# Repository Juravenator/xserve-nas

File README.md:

# xServe infra deployer

This repo is used to manage the NixOS server.

## Quick start

- Check up on CI/CD sync jobs status:
  See the [CICD docs](./docs/cicd.md).
- Sync a specific server on the local machine:
  See the [manually syncing](./docs/manual-sync.md) docs.
- Add a new server, or recommission an existing one:  
  See the docs in [the init folder](./init).

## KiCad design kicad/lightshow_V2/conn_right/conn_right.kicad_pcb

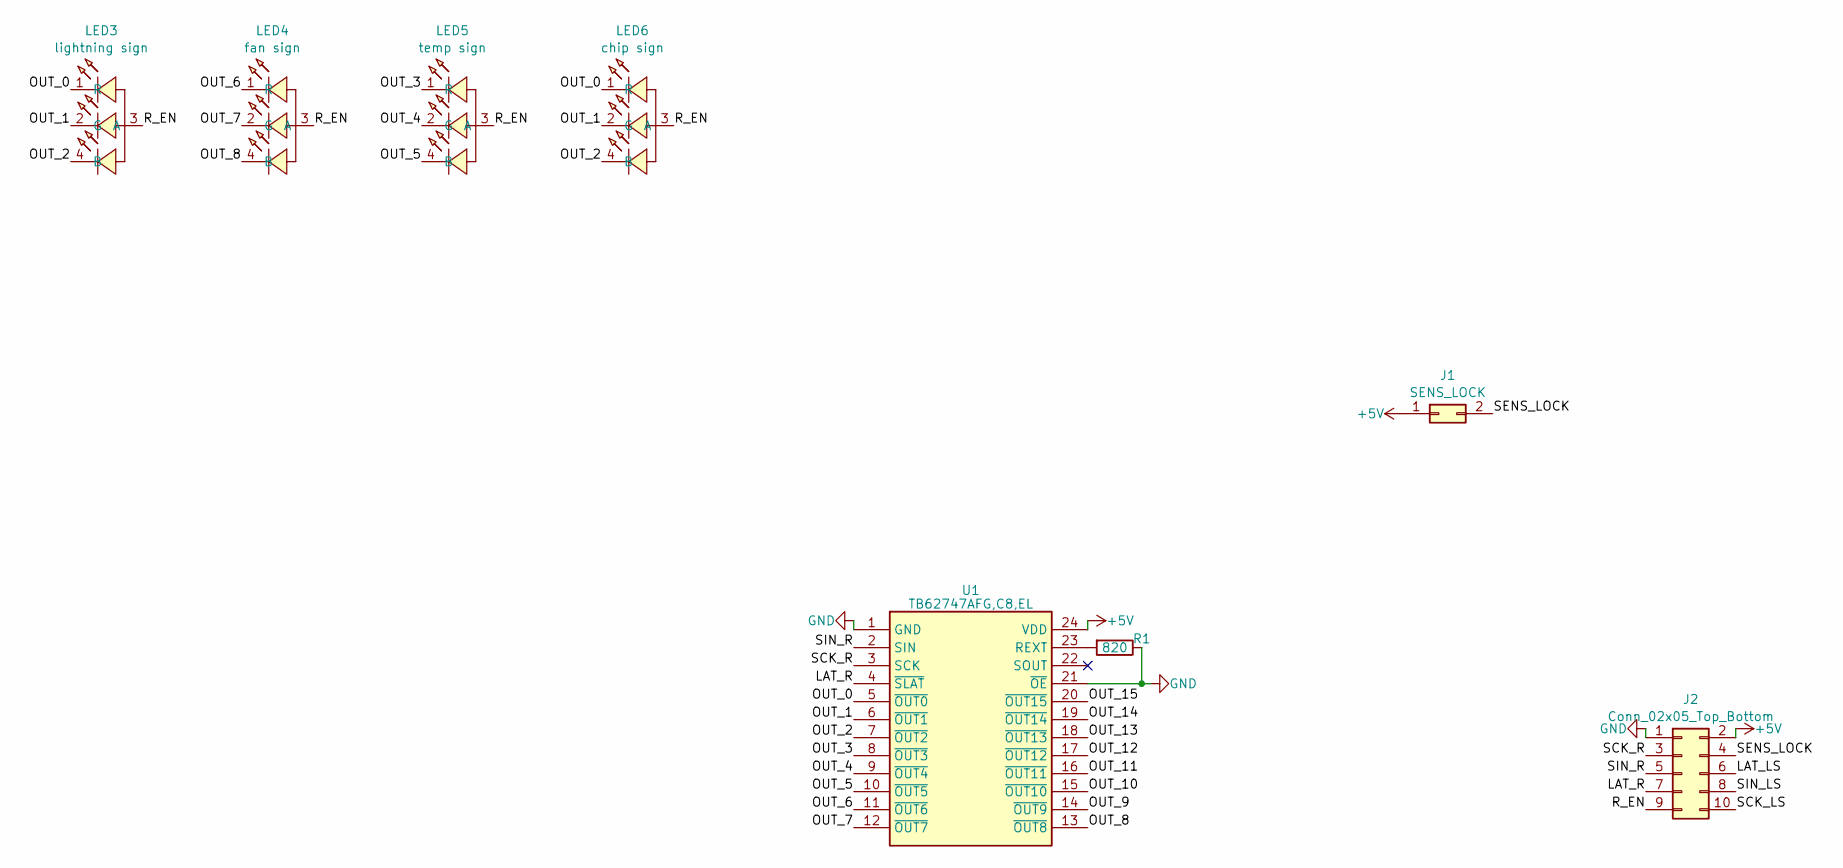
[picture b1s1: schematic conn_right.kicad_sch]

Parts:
J1: SENS_LOCK; PinHeader_1x02_P1.50mm_Vertical
J2: Conn_02x05_Top_Bottom; PinHeader_2x05_P2.00mm_Vertical_SMD
LED3: lightning sign; LED RGB XINGLIGHT XL-2012RGBC 0805; LCSC Part C965848
LED4: fan sign; LED RGB XINGLIGHT XL-2012RGBC 0805; LCSC Part C965848
LED5: temp sign; LED RGB XINGLIGHT XL-2012RGBC 0805; LCSC Part C965848
LED6: chip sign; LED RGB XINGLIGHT XL-2012RGBC 0805; LCSC Part C965848
R1: 820; R_0603_1608Metric
U1: TB62747AFG,C8,EL; SOP100P800X190-24N; Mouser Part Number 757-TB62747AFG,C8,EL

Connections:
+5V: J1.1, J2.2, U1.24 (VDD)
/LAT_LS: J2.6
/LAT_R: J2.7, U1.4 (~SLAT)
/OUT_0: LED3.1 (R), LED6.1 (R), U1.5 (~OUT0)
/OUT_1: LED3.2 (G), LED6.2 (G), U1.6 (~OUT1)
/OUT_2: LED3.4 (B), LED6.4 (B), U1.7 (~OUT2)
/OUT_3: LED5.1 (R), U1.8 (~OUT3)
/OUT_4: LED5.2 (G), U1.9 (~OUT4)
/OUT_5: LED5.4 (B), U1.10 (~OUT5)
/OUT_6: LED4.1 (R), U1.11 (~OUT6)
/OUT_7: LED4.2 (G), U1.12 (~OUT7)
/OUT_8: LED4.4 (B), U1.13 (~OUT8)
/OUT_9: U1.14 (~OUT9)
/OUT_10: U1.15 (~OUT10)
/OUT_11: U1.16 (~OUT11)
/OUT_12: U1.17 (~OUT12)
/OUT_13: U1.18 (~OUT13)
/OUT_14: U1.19 (~OUT14)
/OUT_15: U1.20 (~OUT15)
/R_EN: J2.9, LED3.3 (A), LED4.3 (A), LED5.3 (A), LED6.3 (A)
/SCK_LS: J2.10
/SCK_R: J2.3, U1.3 (SCK)
/SENS_LOCK: J1.2, J2.4
/SIN_LS: J2.8
/SIN_R: J2.5, U1.2 (SIN)
GND: J2.1, R1.1, U1.1 (GND), U1.21 (~OE)
unnamed: R1.2, U1.23 (REXT)

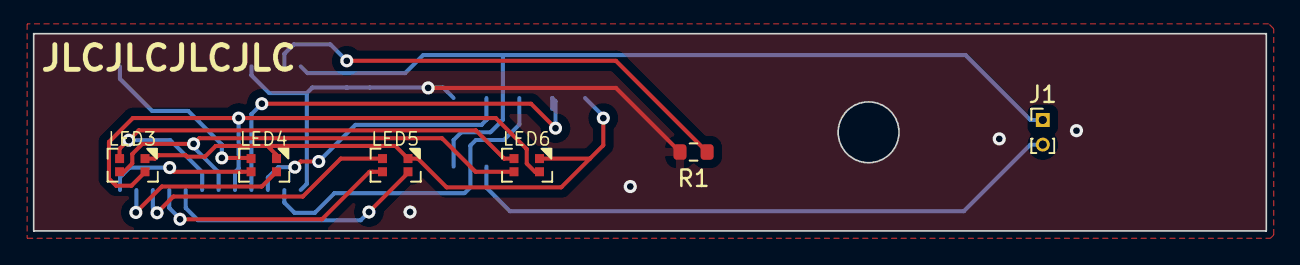
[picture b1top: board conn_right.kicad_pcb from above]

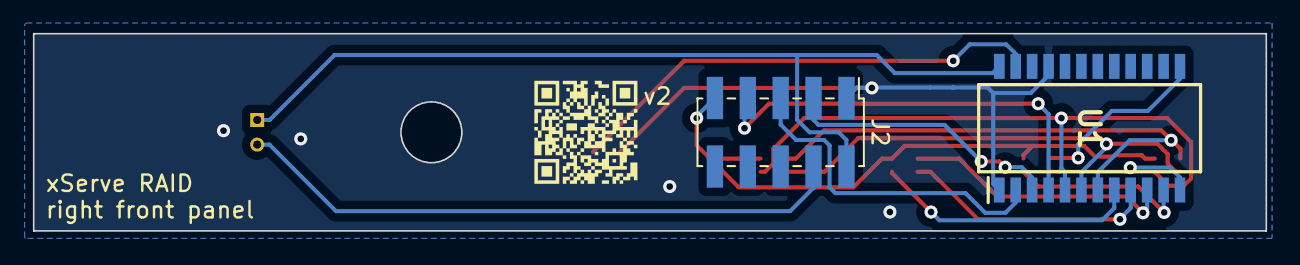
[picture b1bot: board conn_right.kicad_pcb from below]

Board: 2 copper layers, 75.0 x 12.0 mm, 9 parts (3 on the bottom side), 17 nets.

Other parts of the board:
v2: LOGO; qr

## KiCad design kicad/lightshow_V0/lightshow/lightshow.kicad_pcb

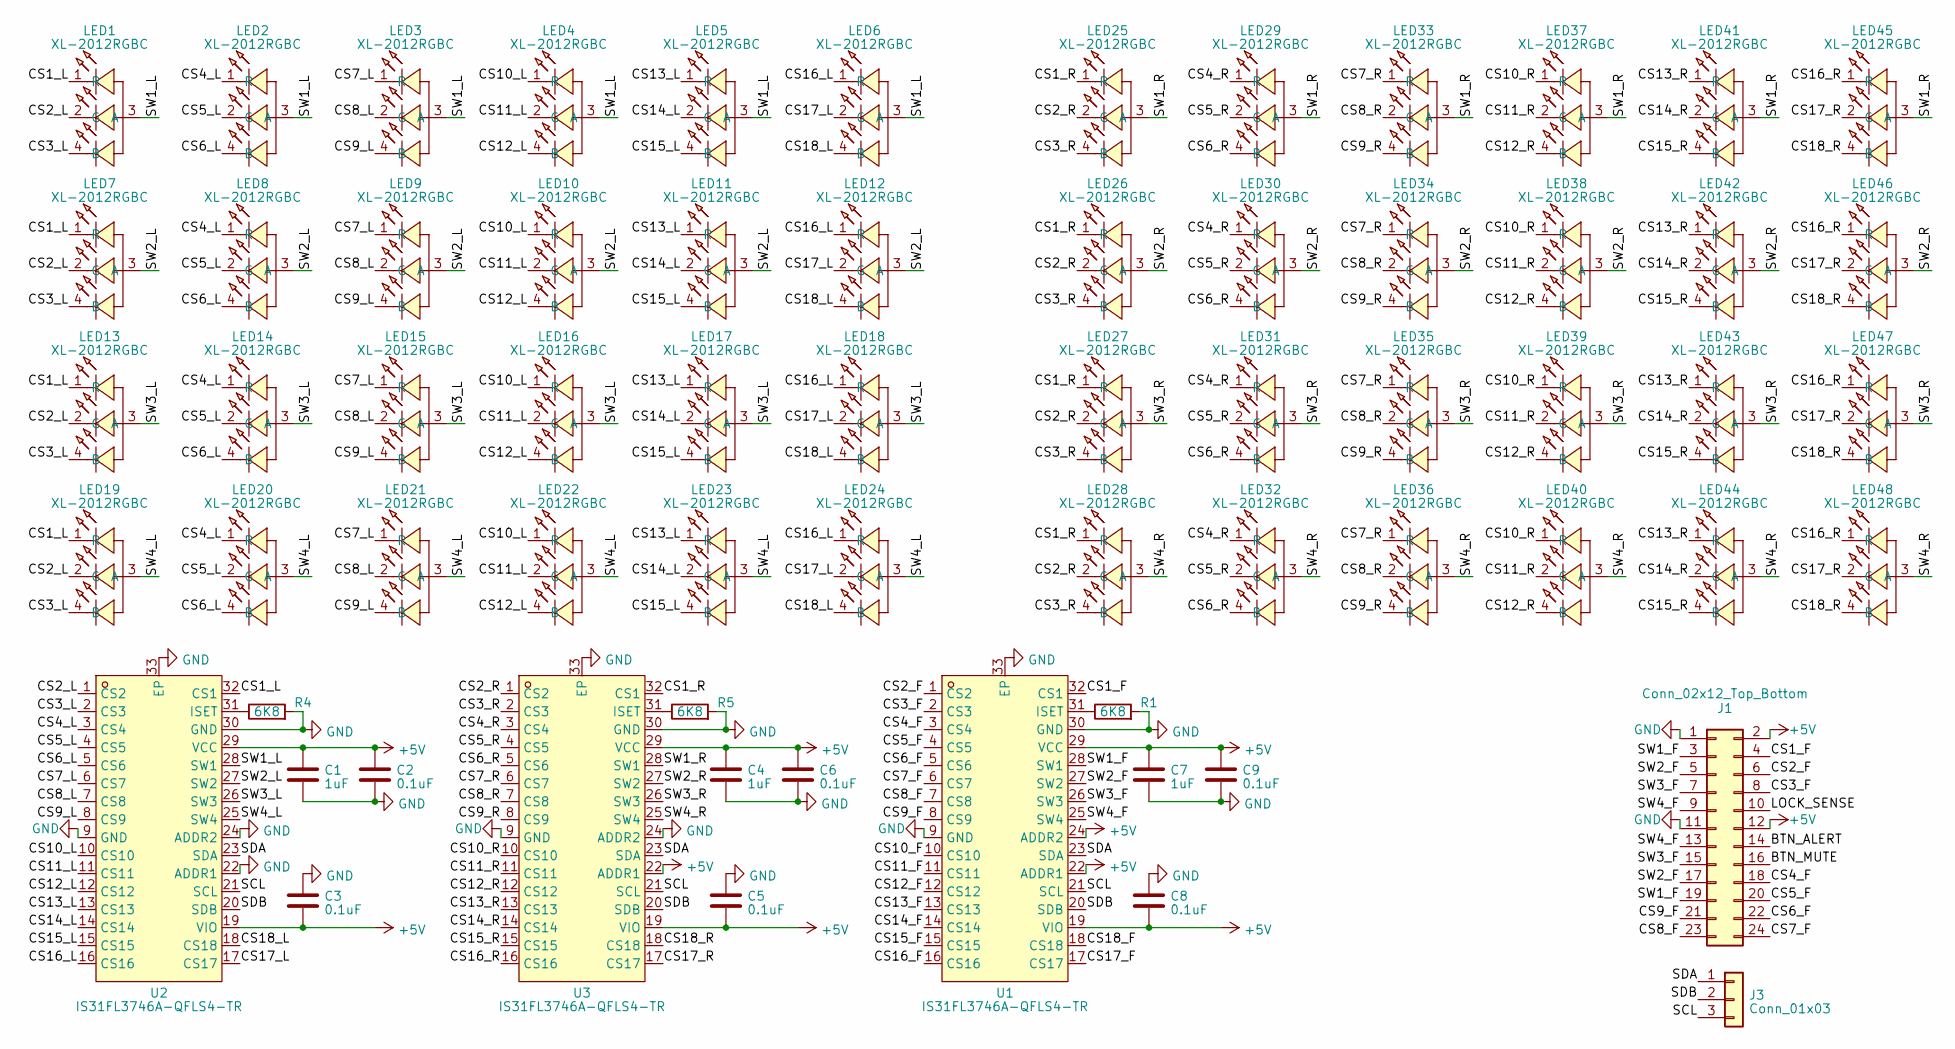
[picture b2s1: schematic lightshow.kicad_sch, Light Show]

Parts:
C1, C4, C7: 1uF; C_0402_1005Metric
C2, C3, C5, C6, C8, C9: 0.1uF; C_0402_1005Metric
J1: Conn_02x12_Top_Bottom; PinHeader_2x12_P2.00mm_Vertical
J3: Conn_01x03; PinHeader_1x03_P2.54mm_Vertical
LED1, LED2, LED3, LED4, LED5, LED6, LED7, LED8, LED9, LED10, LED11, LED12, LED13, LED14, LED15, LED16, LED17, LED18, LED19, LED20, LED21, LED22, LED23, LED24, LED25, LED26, LED27, LED28, LED29, LED30, LED31, LED32, LED33, LED34, LED35, LED36, LED37, LED38, LED39, LED40, LED41, LED42, LED43, LED44, LED45, LED46, LED47, LED48: XL-2012RGBC; LED RGB XINGLIGHT XL-2012RGBC 0805; LCSC Part C965848
R1, R4, R5: 6K8; R_0402_1005Metric
U1, U2, U3: IS31FL3746A-QFLS4-TR; QFN-32_L4.0-W4.0-P0.40-BL-EP2.8; LCSC Part C2961656

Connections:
+5V: C1.1, C2.1, C3.2, C4.1, C5.2, C6.1, C7.1, C8.2, C9.1, J1.2, J1.12, U1.19 (VIO), U1.22 (ADDR1), U1.24 (ADDR2), U1.29 (VCC), U2.19 (VIO), U2.29 (VCC), U3.19 (VIO), U3.22 (ADDR1), U3.29 (VCC)
/BTN_ALERT: J1.14
/BTN_MUTE: J1.16
/CS1_F: J1.4, U1.32 (CS1)
/CS1_L: LED1.1 (R), LED7.1 (R), LED13.1 (R), LED19.1 (R), U2.32 (CS1)
/CS1_R: LED25.1 (R), LED26.1 (R), LED27.1 (R), LED28.1 (R), U3.32 (CS1)
/CS2_F: J1.6, U1.1 (CS2)
/CS2_L: LED1.2 (G), LED7.2 (G), LED13.2 (G), LED19.2 (G), U2.1 (CS2)
/CS2_R: LED25.2 (G), LED26.2 (G), LED27.2 (G), LED28.2 (G), U3.1 (CS2)
/CS3_F: J1.8, U1.2 (CS3)
/CS3_L: LED1.4 (B), LED7.4 (B), LED13.4 (B), LED19.4 (B), U2.2 (CS3)
/CS3_R: LED25.4 (B), LED26.4 (B), LED27.4 (B), LED28.4 (B), U3.2 (CS3)
/CS4_F: J1.18, U1.3 (CS4)
/CS4_L: LED2.1 (R), LED8.1 (R), LED14.1 (R), LED20.1 (R), U2.3 (CS4)
/CS4_R: LED29.1 (R), LED30.1 (R), LED31.1 (R), LED32.1 (R), U3.3 (CS4)
/CS5_F: J1.20, U1.4 (CS5)
/CS5_L: LED2.2 (G), LED8.2 (G), LED14.2 (G), LED20.2 (G), U2.4 (CS5)
/CS5_R: LED29.2 (G), LED30.2 (G), LED31.2 (G), LED32.2 (G), U3.4 (CS5)
/CS6_F: J1.22, U1.5 (CS6)
/CS6_L: LED2.4 (B), LED8.4 (B), LED14.4 (B), LED20.4 (B), U2.5 (CS6)
/CS6_R: LED29.4 (B), LED30.4 (B), LED31.4 (B), LED32.4 (B), U3.5 (CS6)
/CS7_F: J1.24, U1.6 (CS7)
/CS7_L: LED3.1 (R), LED9.1 (R), LED15.1 (R), LED21.1 (R), U2.6 (CS7)
/CS7_R: LED33.1 (R), LED34.1 (R), LED35.1 (R), LED36.1 (R), U3.6 (CS7)
/CS8_F: J1.23, U1.7 (CS8)
/CS8_L: LED3.2 (G), LED9.2 (G), LED15.2 (G), LED21.2 (G), U2.7 (CS8)
/CS8_R: LED33.2 (G), LED34.2 (G), LED35.2 (G), LED36.2 (G), U3.7 (CS8)
/CS9_F: J1.21, U1.8 (CS9)
/CS9_L: LED3.4 (B), LED9.4 (B), LED15.4 (B), LED21.4 (B), U2.8 (CS9)
/CS9_R: LED33.4 (B), LED34.4 (B), LED35.4 (B), LED36.4 (B), U3.8 (CS9)
/CS10_F: U1.10 (CS10)
/CS10_L: LED4.1 (R), LED10.1 (R), LED16.1 (R), LED22.1 (R), U2.10 (CS10)
/CS10_R: LED37.1 (R), LED38.1 (R), LED39.1 (R), LED40.1 (R), U3.10 (CS10)
/CS11_F: U1.11 (CS11)
/CS11_L: LED4.2 (G), LED10.2 (G), LED16.2 (G), LED22.2 (G), U2.11 (CS11)
/CS11_R: LED37.2 (G), LED38.2 (G), LED39.2 (G), LED40.2 (G), U3.11 (CS11)
/CS12_F: U1.12 (CS12)
/CS12_L: LED4.4 (B), LED10.4 (B), LED16.4 (B), LED22.4 (B), U2.12 (CS12)
/CS12_R: LED37.4 (B), LED38.4 (B), LED39.4 (B), LED40.4 (B), U3.12 (CS12)
/CS13_F: U1.13 (CS13)
/CS13_L: LED5.1 (R), LED11.1 (R), LED17.1 (R), LED23.1 (R), U2.13 (CS13)
/CS13_R: LED41.1 (R), LED42.1 (R), LED43.1 (R), LED44.1 (R), U3.13 (CS13)
/CS14_F: U1.14 (CS14)
/CS14_L: LED5.2 (G), LED11.2 (G), LED17.2 (G), LED23.2 (G), U2.14 (CS14)
/CS14_R: LED41.2 (G), LED42.2 (G), LED43.2 (G), LED44.2 (G), U3.14 (CS14)
/CS15_F: U1.15 (CS15)
/CS15_L: LED5.4 (B), LED11.4 (B), LED17.4 (B), LED23.4 (B), U2.15 (CS15)
/CS15_R: LED41.4 (B), LED42.4 (B), LED43.4 (B), LED44.4 (B), U3.15 (CS15)
/CS16_F: U1.16 (CS16)
/CS16_L: LED6.1 (R), LED12.1 (R), LED18.1 (R), LED24.1 (R), U2.16 (CS16)
/CS16_R: LED45.1 (R), LED46.1 (R), LED47.1 (R), LED48.1 (R), U3.16 (CS16)
/CS17_F: U1.17 (CS17)
/CS17_L: LED6.2 (G), LED12.2 (G), LED18.2 (G), LED24.2 (G), U2.17 (CS17)
/CS17_R: LED45.2 (G), LED46.2 (G), LED47.2 (G), LED48.2 (G), U3.17 (CS17)
/CS18_F: U1.18 (CS18)
/CS18_L: LED6.4 (B), LED12.4 (B), LED18.4 (B), LED24.4 (B), U2.18 (CS18)
/CS18_R: LED45.4 (B), LED46.4 (B), LED47.4 (B), LED48.4 (B), U3.18 (CS18)
/LOCK_SENSE: J1.10
/SCL: J3.3, U1.21 (SCL), U2.21 (SCL), U3.21 (SCL)
/SDA: J3.1, U1.23 (SDA), U2.23 (SDA), U3.23 (SDA)
/SDB: J3.2, U1.20 (SDB), U2.20 (SDB), U3.20 (SDB)
/SW1_F: J1.3, J1.19, U1.28 (SW1)
/SW1_L: LED1.3 (A), LED2.3 (A), LED3.3 (A), LED4.3 (A), LED5.3 (A), LED6.3 (A), U2.28 (SW1)
/SW1_R: LED25.3 (A), LED29.3 (A), LED33.3 (A), LED37.3 (A), LED41.3 (A), LED45.3 (A), U3.28 (SW1)
/SW2_F: J1.5, J1.17, U1.27 (SW2)
/SW2_L: LED7.3 (A), LED8.3 (A), LED9.3 (A), LED10.3 (A), LED11.3 (A), LED12.3 (A), U2.27 (SW2)
/SW2_R: LED26.3 (A), LED30.3 (A), LED34.3 (A), LED38.3 (A), LED42.3 (A), LED46.3 (A), U3.27 (SW2)
/SW3_F: J1.7, J1.15, U1.26 (SW3)
/SW3_L: LED13.3 (A), LED14.3 (A), LED15.3 (A), LED16.3 (A), LED17.3 (A), LED18.3 (A), U2.26 (SW3)
/SW3_R: LED27.3 (A), LED31.3 (A), LED35.3 (A), LED39.3 (A), LED43.3 (A), LED47.3 (A), U3.26 (SW3)
/SW4_F: J1.9, J1.13, U1.25 (SW4)
/SW4_L: LED19.3 (A), LED20.3 (A), LED21.3 (A), LED22.3 (A), LED23.3 (A), LED24.3 (A), U2.25 (SW4)
/SW4_R: LED28.3 (A), LED32.3 (A), LED36.3 (A), LED40.3 (A), LED44.3 (A), LED48.3 (A), U3.25 (SW4)
GND: C1.2, C2.2, C3.1, C4.2, C5.1, C6.2, C7.2, C8.1, C9.2, J1.1, J1.11, R1.2, R4.2, R5.2, U1.9 (GND), U1.30 (GND), U1.33 (EP), U2.9 (GND), U2.22 (ADDR1), U2.24 (ADDR2), U2.30 (GND), U2.33 (EP), U3.9 (GND), U3.24 (ADDR2), U3.30 (GND), U3.33 (EP)
unnamed: R1.1, U1.31 (ISET)
unnamed: R4.1, U2.31 (ISET)
unnamed: R5.1, U3.31 (ISET)

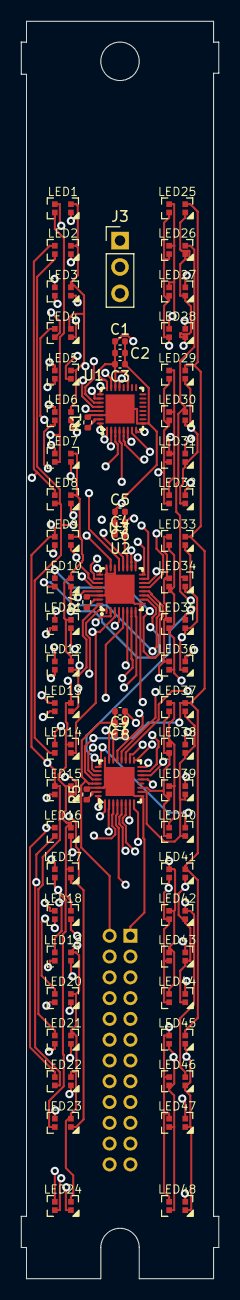
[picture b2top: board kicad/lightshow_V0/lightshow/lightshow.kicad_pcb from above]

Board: 8 copper layers, 19.0 x 121.0 mm, 65 parts (1 on the bottom side), 65 nets.

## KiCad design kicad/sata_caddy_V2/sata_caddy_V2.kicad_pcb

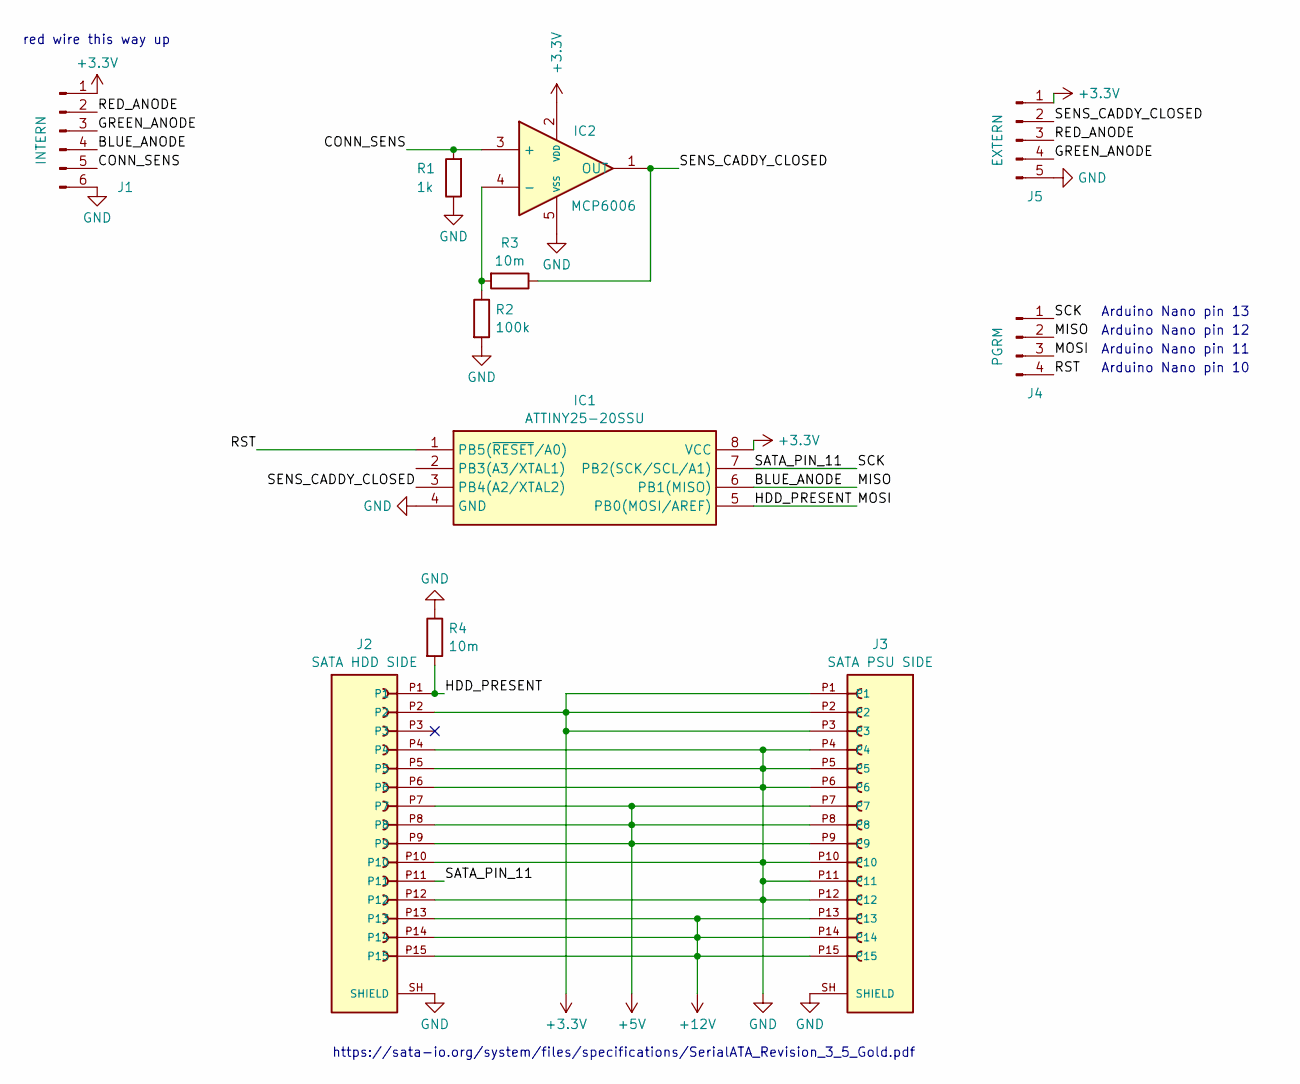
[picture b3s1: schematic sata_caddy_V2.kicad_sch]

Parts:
IC1: ATTINY25-20SSU; SOIC127P600X175-8N; Mouser Part Number 556-ATTINY25-20SSU
IC2: MCP6006; SOT95P270X145-5N; Mouser Part Number 579-MCP6006RT-E/OT
J1: INTERN; PinHeader_1x06_P2.54mm_Vertical
J2: SATA HDD SIDE; sata_standing_female; PARTREV M
J3: SATA PSU SIDE; sata_standing_male_snip; PARTREV M
J4: PGRM; PinHeader_1x04_P2.54mm_Vertical
J5: EXTERN; PinHeader_1x05_P2.54mm_Vertical
R1: 1k; R_Axial_DIN0204_L3.6mm_D1.6mm_P7.62mm_Horizontal
R2: 100k; R_Axial_DIN0204_L3.6mm_D1.6mm_P7.62mm_Horizontal
R3, R4: 10m; R_Axial_DIN0204_L3.6mm_D1.6mm_P7.62mm_Horizontal

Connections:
+3.3V: IC1.8 (VCC), IC2.2 (VDD), J1.1, J2.P2, J3.P1, J3.P2, J3.P3, J5.1
+5V: J2.P7, J2.P8, J2.P9, J3.P7, J3.P8, J3.P9
+12V: J2.P13, J2.P14, J2.P15, J3.P13, J3.P14, J3.P15
/BLUE_ANODE: IC1.6 (PB1(MISO)), J1.4, J4.2
/CONN_SENS: IC2.3 (+), J1.5, R1.2
/GREEN_ANODE: J1.3, J5.4
/HDD_PRESENT: IC1.5 (PB0(MOSI/AREF)), J2.P1, J4.3, R4.2
/RED_ANODE: J1.2, J5.3
/RST: IC1.1 (PB5(~RESET/A0)), J4.4
/SATA_PIN_11: IC1.7 (PB2(SCK/SCL/A1)), J2.P11, J4.1
/SENS_CADDY_CLOSED: IC1.3 (PB4(A2/XTAL2)), IC2.1 (OUT), J5.2, R3.1
GND: IC1.4 (GND), IC2.5 (VSS), J1.6, J2.P4, J2.P5, J2.P6, J2.P10, J2.P12, J2.SH (SHIELD), J3.P4, J3.P5, J3.P6, J3.P10, J3.P11, J3.P12, J3.SH (SHIELD), J5.5, R1.1, R2.2, R4.1
unnamed: IC2.4 (-), R2.1, R3.2

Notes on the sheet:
Arduino Nano pin 11
Arduino Nano pin 13
Arduino Nano pin 10
Arduino Nano pin 12
red wire this way up
https://sata-io.org/system/files/specifications/SerialATA_Revision_3_5_Gold.pdf

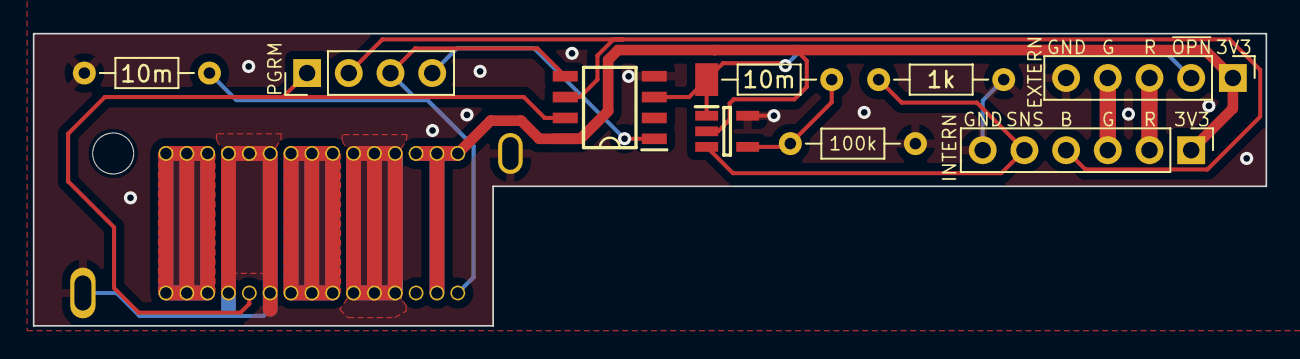
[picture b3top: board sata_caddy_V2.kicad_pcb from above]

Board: 2 copper layers, 75.1 x 17.8 mm, 12 parts (1 on the bottom side), 13 nets.

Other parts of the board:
v2: LOGO; qr

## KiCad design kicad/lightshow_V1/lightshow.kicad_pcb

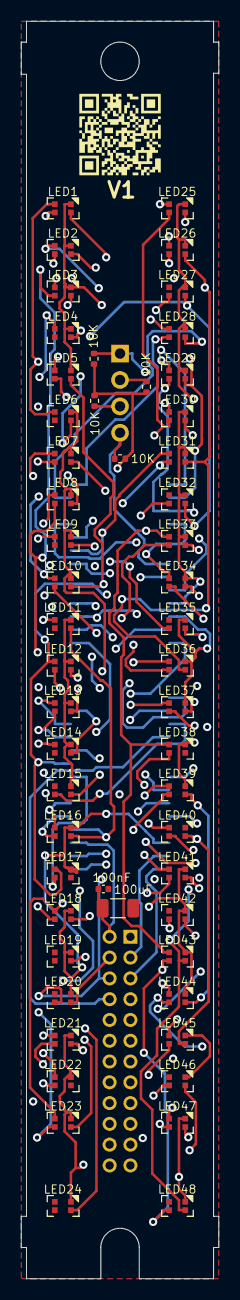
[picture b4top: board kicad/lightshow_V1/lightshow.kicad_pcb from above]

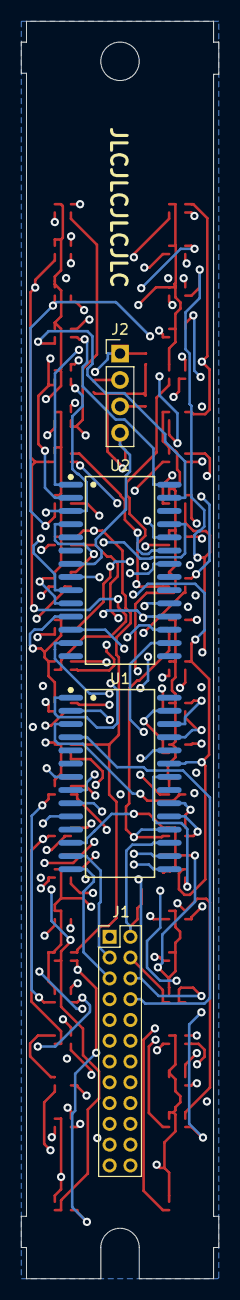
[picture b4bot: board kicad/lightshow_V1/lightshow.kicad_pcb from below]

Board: 4 copper layers, 19.0 x 121.0 mm, 59 parts (4 on the bottom side), 52 nets.

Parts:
C1: 100nF; C_0402_1005Metric
C2: 100uF; C_1206_3216Metric
J1: Conn_02x12_Top_Bottom; PinHeader_2x12_P2.00mm_Vertical
J2: Conn_01x04; PinHeader_1x04_P2.54mm_Vertical
LED1, LED2, LED3, LED4, LED5, LED6, LED7, LED8, LED9, LED10, LED11, LED12, LED13, LED14, LED15, LED16, LED17, LED18, LED19, LED20, LED21, LED22, LED23, LED24, LED25, LED26, LED27, LED28, LED29, LED30, LED31, LED32, LED33, LED34, LED35, LED36, LED37, LED38, LED39, LED40, LED41, LED42, LED43, LED44, LED45, LED46, LED47, LED48: XL-2012RGBC; LED RGB XINGLIGHT XL-2012RGBC 0805
R1, R2, R3, R4: 10K; R_0402_1005Metric
U1, U2: TM1640; SOIC-28_L17.9-W7.5-P1.27-LS10.3-BL
v1: LOGO

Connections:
+5V: C1.1, C2.1, J1.2, J1.12, R1.2, R2.2, R3.2, R4.2, U1.17 (VDD), U2.17 (VDD)
/CLK2: J2.3, R4.1, U2.8 (SCLK)
/CLK_1: J2.1, R3.1, U1.8 (SCLK)
/DIN1: J2.2, R1.1, U1.7 (DIN)
/DIN2: J2.4, R2.1, U2.7 (DIN)
/GRID1_1: LED1.1 (R), LED6.1 (R), LED11.1 (R), LED16.1 (R), LED21.1 (R), U1.18 (GRID1)
/GRID1_2: LED1.2 (G), LED6.2 (G), LED11.2 (G), LED16.2 (G), LED21.2 (G), U1.19 (GRID2)
/GRID1_3: LED1.4 (B), LED6.4 (B), LED11.4 (B), LED16.4 (B), LED21.4 (B), U1.20 (GRID3)
/GRID1_4: LED2.1 (R), LED7.1 (R), LED12.1 (R), LED17.1 (R), LED22.1 (R), U1.21 (GRID4)
/GRID1_5: LED2.2 (G), LED7.2 (G), LED12.2 (G), LED17.2 (G), LED22.2 (G), U1.22 (GRID5)
/GRID1_6: LED2.4 (B), LED7.4 (B), LED12.4 (B), LED17.4 (B), LED22.4 (B), U1.23 (GRID6)
/GRID1_7: LED3.1 (R), LED8.1 (R), LED13.1 (R), LED18.1 (R), LED23.1 (R), U1.24 (GRID7)
/GRID1_8: LED3.2 (G), LED8.2 (G), LED13.2 (G), LED18.2 (G), LED23.2 (G), U1.25 (GRID8)
/GRID1_9: LED3.4 (B), LED8.4 (B), LED13.4 (B), LED18.4 (B), LED23.4 (B), U1.26 (GRID9)
/GRID1_10: LED4.1 (R), LED9.1 (R), LED14.1 (R), LED19.1 (R), LED24.1 (R), U1.27 (GRID10)
/GRID1_11: LED4.2 (G), LED9.2 (G), LED14.2 (G), LED19.2 (G), LED24.2 (G), U1.28 (GRID11)
/GRID1_12: LED4.4 (B), LED9.4 (B), LED14.4 (B), LED19.4 (B), LED24.4 (B), U1.1 (GRID12)
/GRID1_13: J1.4, LED5.1 (R), LED10.1 (R), LED15.1 (R), LED20.1 (R), U1.2 (GRID13)
/GRID1_14: J1.6, LED5.2 (G), LED10.2 (G), LED15.2 (G), LED20.2 (G), U1.3 (GRID14)
/GRID1_15: J1.8, LED5.4 (B), LED10.4 (B), LED15.4 (B), LED20.4 (B), U1.4 (GRID15)
/GRID2_1: J1.13, LED25.1 (R), LED30.1 (R), LED35.1 (R), LED40.1 (R), LED45.1 (R), U2.18 (GRID1)
/GRID2_2: J1.15, LED25.2 (G), LED30.2 (G), LED35.2 (G), LED40.2 (G), LED45.2 (G), U2.19 (GRID2)
/GRID2_3: J1.17, LED25.4 (B), LED30.4 (B), LED35.4 (B), LED40.4 (B), LED45.4 (B), U2.20 (GRID3)
/GRID2_4: LED26.1 (R), LED31.1 (R), LED36.1 (R), LED41.1 (R), LED46.1 (R), U2.21 (GRID4)
/GRID2_5: LED26.2 (G), LED31.2 (G), LED36.2 (G), LED41.2 (G), LED46.2 (G), U2.22 (GRID5)
/GRID2_6: LED26.4 (B), LED31.4 (B), LED36.4 (B), LED41.4 (B), LED46.4 (B), U2.23 (GRID6)
/GRID2_7: LED27.1 (R), LED32.1 (R), LED37.1 (R), LED42.1 (R), LED47.1 (R), U2.24 (GRID7)
/GRID2_8: LED27.2 (G), LED32.2 (G), LED37.2 (G), LED42.2 (G), LED47.2 (G), U2.25 (GRID8)
/GRID2_9: LED27.4 (B), LED32.4 (B), LED37.4 (B), LED42.4 (B), LED47.4 (B), U2.26 (GRID9)
/GRID2_10: LED28.1 (R), LED33.1 (R), LED38.1 (R), LED43.1 (R), LED48.1 (R), U2.27 (GRID10)
/GRID2_11: LED28.2 (G), LED33.2 (G), LED38.2 (G), LED43.2 (G), LED48.2 (G), U2.28 (GRID11)
/GRID2_12: LED28.4 (B), LED33.4 (B), LED38.4 (B), LED43.4 (B), LED48.4 (B), U2.1 (GRID12)
/GRID2_13: J1.19, LED29.1 (R), LED34.1 (R), LED39.1 (R), LED44.1 (R), U2.2 (GRID13)
/GRID2_14: J1.21, LED29.2 (G), LED34.2 (G), LED39.2 (G), LED44.2 (G), U2.3 (GRID14)
/GRID2_15: J1.23, LED29.4 (B), LED34.4 (B), LED39.4 (B), LED44.4 (B), U2.4 (GRID15)
/SEG1_1: LED1.3 (A), LED2.3 (A), LED3.3 (A), LED4.3 (A), LED5.3 (A), U1.9 (SEG1)
/SEG1_2: LED6.3 (A), LED7.3 (A), LED8.3 (A), LED9.3 (A), LED10.3 (A), U1.10 (SEG2)
/SEG1_3: LED11.3 (A), LED12.3 (A), LED13.3 (A), LED14.3 (A), LED15.3 (A), U1.11 (SEG3)
/SEG1_4: LED16.3 (A), LED17.3 (A), LED18.3 (A), LED19.3 (A), LED20.3 (A), U1.12 (SEG4)
/SEG1_5: J1.3, LED21.3 (A), LED22.3 (A), LED23.3 (A), LED24.3 (A), U1.13 (SEG5)
/SEG1_6: J1.5, U1.14 (SEG6)
/SEG1_7: J1.7, U1.15 (SEG7)
/SEG1_8: J1.9, U1.16 (SEG8)
/SEG2_1: LED25.3 (A), LED26.3 (A), LED27.3 (A), LED28.3 (A), LED29.3 (A), U2.9 (SEG1)
/SEG2_2: LED30.3 (A), LED31.3 (A), LED32.3 (A), LED33.3 (A), LED34.3 (A), U2.10 (SEG2)
/SEG2_3: LED35.3 (A), LED36.3 (A), LED37.3 (A), LED38.3 (A), LED39.3 (A), U2.11 (SEG3)
/SEG2_4: LED40.3 (A), LED41.3 (A), LED42.3 (A), LED43.3 (A), LED44.3 (A), U2.12 (SEG4)
/SEG2_5: LED45.3 (A), LED46.3 (A), LED47.3 (A), LED48.3 (A), U2.13 (SEG5)
/SEG2_6: J1.18, U2.14 (SEG6)
/SEG2_7: J1.20, U2.15 (SEG7)
/SEG2_8: J1.22, U2.16 (SEG8)
GND: C1.2, C2.2, J1.1, J1.11, U1.6 (VSS), U2.6 (VSS)

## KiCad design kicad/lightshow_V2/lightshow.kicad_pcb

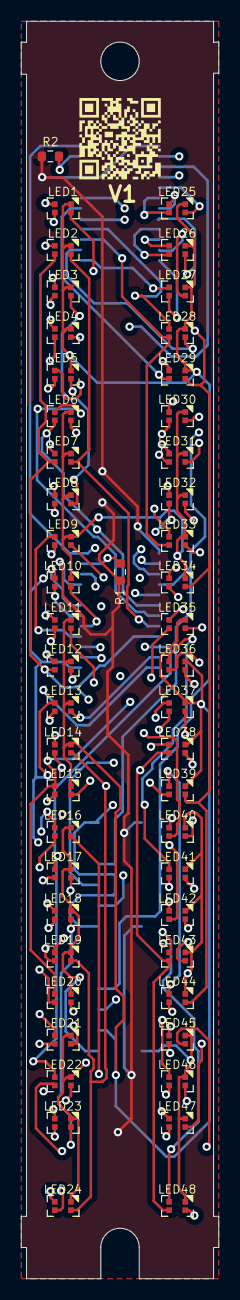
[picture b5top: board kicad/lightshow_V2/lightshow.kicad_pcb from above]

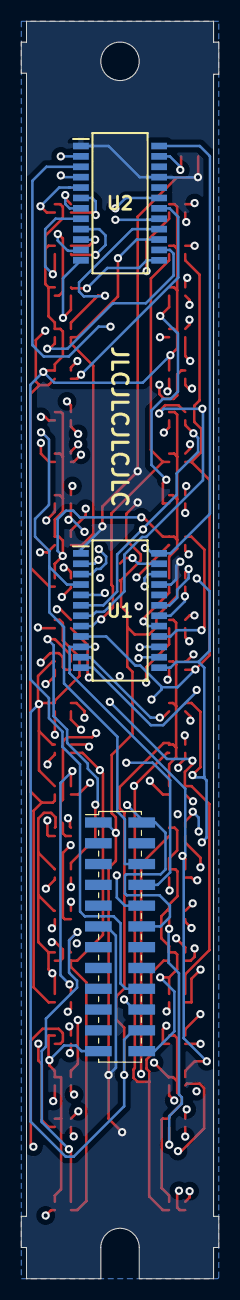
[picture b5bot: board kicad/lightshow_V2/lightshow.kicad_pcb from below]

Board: 4 copper layers, 19.0 x 121.0 mm, 54 parts (3 on the bottom side), 43 nets.

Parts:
J1: Conn_02x12_Top_Bottom; PinHeader_2x12_P2.00mm_Vertical_SMD
LED1, LED2, LED3, LED4, LED5, LED6, LED7, LED8, LED9, LED10, LED11, LED12, LED13, LED14, LED15, LED16, LED17, LED18, LED19, LED20, LED21, LED22, LED23, LED24, LED25, LED26, LED27, LED28, LED29, LED30, LED31, LED32, LED33, LED34, LED35, LED36, LED37, LED38, LED39, LED40, LED41, LED42, LED43, LED44, LED45, LED46, LED47, LED48: XL-2012RGBC; LED RGB XINGLIGHT XL-2012RGBC 0805
R1, R2: 820; R_0603_1608Metric
U1, U2: TB62747AFG,C8,EL; SOP100P800X190-24N
v1: LOGO

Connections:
+5V: J1.2, J1.12, U1.24 (VDD), U2.24 (VDD)
/L1_EN: J1.18, LED1.3 (A), LED2.3 (A), LED3.3 (A), LED4.3 (A), LED5.3 (A), LED25.3 (A), LED26.3 (A), LED27.3 (A), LED28.3 (A), LED29.3 (A)
/L2_EN: J1.20, LED6.3 (A), LED7.3 (A), LED8.3 (A), LED9.3 (A), LED10.3 (A), LED30.3 (A), LED31.3 (A), LED32.3 (A), LED33.3 (A), LED34.3 (A)
/L3_EN: J1.22, LED11.3 (A), LED12.3 (A), LED13.3 (A), LED14.3 (A), LED15.3 (A), LED35.3 (A), LED36.3 (A), LED37.3 (A), LED38.3 (A), LED39.3 (A)
/L4_EN: J1.24, LED16.3 (A), LED17.3 (A), LED18.3 (A), LED19.3 (A), LED20.3 (A), LED40.3 (A), LED41.3 (A), LED42.3 (A), LED43.3 (A), LED44.3 (A)
/L5_EN: J1.23, LED21.3 (A), LED22.3 (A), LED23.3 (A), LED24.3 (A), LED45.3 (A), LED46.3 (A), LED47.3 (A), LED48.3 (A)
/LAT_LS: J1.6, U1.4 (~SLAT), U2.4 (~SLAT)
/OUTL_0: LED1.1 (R), LED6.1 (R), LED11.1 (R), LED16.1 (R), LED21.1 (R), U1.5 (~OUT0)
/OUTL_1: LED1.2 (G), LED6.2 (G), LED11.2 (G), LED16.2 (G), LED21.2 (G), U1.6 (~OUT1)
/OUTL_2: LED1.4 (B), LED6.4 (B), LED11.4 (B), LED16.4 (B), LED21.4 (B), U1.7 (~OUT2)
/OUTL_3: LED2.1 (R), LED7.1 (R), LED12.1 (R), LED17.1 (R), LED22.1 (R), U1.8 (~OUT3)
/OUTL_4: LED2.2 (G), LED7.2 (G), LED12.2 (G), LED17.2 (G), LED22.2 (G), U1.9 (~OUT4)
/OUTL_5: LED2.4 (B), LED7.4 (B), LED12.4 (B), LED17.4 (B), LED22.4 (B), U1.10 (~OUT5)
/OUTL_6: LED3.1 (R), LED8.1 (R), LED13.1 (R), LED18.1 (R), LED23.1 (R), U1.11 (~OUT6)
/OUTL_7: LED3.2 (G), LED8.2 (G), LED13.2 (G), LED18.2 (G), LED23.2 (G), U1.12 (~OUT7)
/OUTL_8: LED3.4 (B), LED8.4 (B), LED13.4 (B), LED18.4 (B), LED23.4 (B), U1.13 (~OUT8)
/OUTL_9: LED4.1 (R), LED9.1 (R), LED14.1 (R), LED19.1 (R), LED24.1 (R), U1.14 (~OUT9)
/OUTL_10: LED4.2 (G), LED9.2 (G), LED14.2 (G), LED19.2 (G), LED24.2 (G), U1.15 (~OUT10)
/OUTL_11: LED4.4 (B), LED9.4 (B), LED14.4 (B), LED19.4 (B), LED24.4 (B), U1.16 (~OUT11)
/OUTL_12: LED5.1 (R), LED10.1 (R), LED15.1 (R), LED20.1 (R), U1.17 (~OUT12)
/OUTL_13: LED5.2 (G), LED10.2 (G), LED15.2 (G), LED20.2 (G), U1.18 (~OUT13)
/OUTL_14: LED5.4 (B), LED10.4 (B), LED15.4 (B), LED20.4 (B), U1.19 (~OUT14)
/OUTR_0: LED25.1 (R), LED30.1 (R), LED35.1 (R), LED40.1 (R), LED45.1 (R), U2.5 (~OUT0)
/OUTR_1: LED25.2 (G), LED30.2 (G), LED35.2 (G), LED40.2 (G), LED45.2 (G), U2.6 (~OUT1)
/OUTR_2: LED25.4 (B), LED30.4 (B), LED35.4 (B), LED40.4 (B), LED45.4 (B), U2.7 (~OUT2)
/OUTR_3: LED26.1 (R), LED31.1 (R), LED36.1 (R), LED41.1 (R), LED46.1 (R), U2.8 (~OUT3)
/OUTR_4: LED26.2 (G), LED31.2 (G), LED36.2 (G), LED41.2 (G), LED46.2 (G), U2.9 (~OUT4)
/OUTR_5: LED26.4 (B), LED31.4 (B), LED36.4 (B), LED41.4 (B), LED46.4 (B), U2.10 (~OUT5)
/OUTR_6: LED27.1 (R), LED32.1 (R), LED37.1 (R), LED42.1 (R), LED47.1 (R), U2.11 (~OUT6)
/OUTR_7: LED27.2 (G), LED32.2 (G), LED37.2 (G), LED42.2 (G), LED47.2 (G), U2.12 (~OUT7)
/OUTR_8: LED27.4 (B), LED32.4 (B), LED37.4 (B), LED42.4 (B), LED47.4 (B), U2.13 (~OUT8)
/OUTR_9: LED28.1 (R), LED33.1 (R), LED38.1 (R), LED43.1 (R), LED48.1 (R), U2.14 (~OUT9)
/OUTR_10: LED28.2 (G), LED33.2 (G), LED38.2 (G), LED43.2 (G), LED48.2 (G), U2.15 (~OUT10)
/OUTR_11: LED28.4 (B), LED33.4 (B), LED38.4 (B), LED43.4 (B), LED48.4 (B), U2.16 (~OUT11)
/OUTR_12: LED29.1 (R), LED34.1 (R), LED39.1 (R), LED44.1 (R), U2.17 (~OUT12)
/OUTR_13: LED29.2 (G), LED34.2 (G), LED39.2 (G), LED44.2 (G), U2.18 (~OUT13)
/OUTR_14: LED29.4 (B), LED34.4 (B), LED39.4 (B), LED44.4 (B), U2.19 (~OUT14)
/SCK_LS: J1.10, U1.3 (SCK), U2.3 (SCK)
/SIN_LS: J1.8, U1.2 (SIN)
GND: J1.1, J1.11, R1.1, R2.1, U1.1 (GND), U1.21 (~OE), U2.1 (GND), U2.21 (~OE)
unnamed: R1.2, U1.23 (REXT)
unnamed: U1.22 (SOUT), U2.2 (SIN)
unnamed: R2.2, U2.23 (REXT)

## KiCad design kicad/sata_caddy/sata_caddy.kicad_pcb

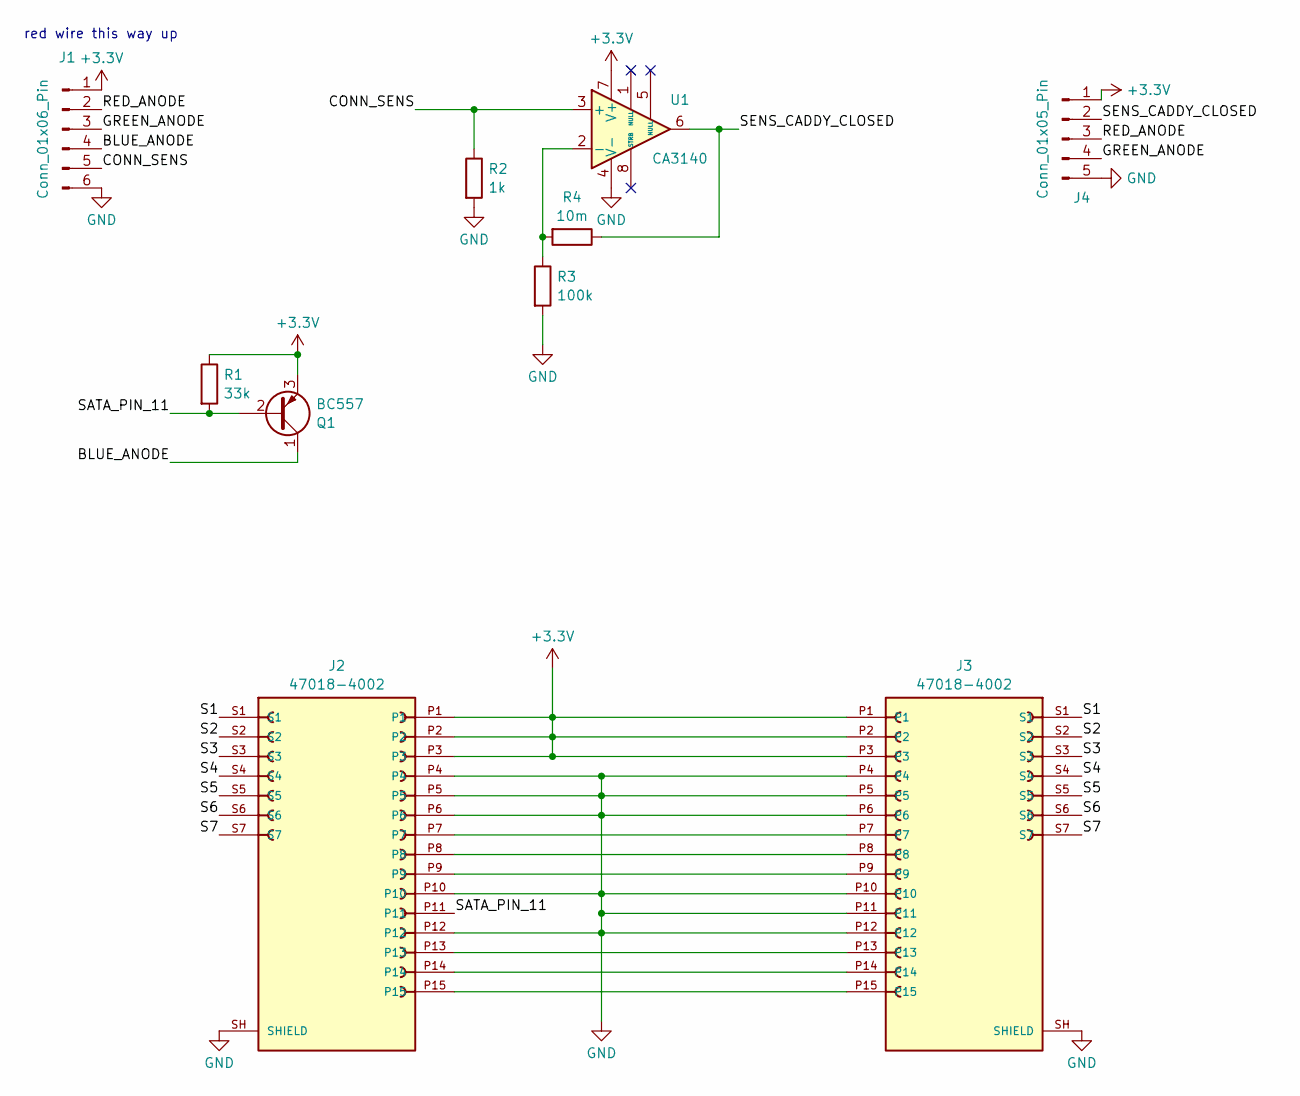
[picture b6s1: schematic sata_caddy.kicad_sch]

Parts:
J1: Conn_01x06_Pin; PinHeader_1x06_P2.54mm_Vertical
J2: 47018-4002; MOLEX_47018-4002_bottom; PARTREV M
J3: 47018-4002; male connector; PARTREV M
J4: Conn_01x05_Pin; PinHeader_1x05_P2.54mm_Vertical
Q1: BC557; TO-92_Inline
R1: 33k; R_Axial_DIN0204_L3.6mm_D1.6mm_P7.62mm_Horizontal
R2: 1k; R_Axial_DIN0204_L3.6mm_D1.6mm_P7.62mm_Horizontal
R3: 100k; R_Axial_DIN0204_L3.6mm_D1.6mm_P7.62mm_Horizontal
R4: 10m; R_Axial_DIN0204_L3.6mm_D1.6mm_P7.62mm_Horizontal
U1: CA3140; DIP-8_W7.62mm

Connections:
+3.3V: J1.1, J2.P1, J2.P2, J2.P3, J3.P1, J3.P2, J3.P3, J4.1, Q1.3 (E), R1.1, U1.7 (V+)
/BLUE_ANODE: J1.4, Q1.1 (C)
/CONN_SENS: J1.5, R2.1, U1.3 (+)
/GREEN_ANODE: J1.3, J4.4
/RED_ANODE: J1.2, J4.3
/S1: J2.S1, J3.S1
/S2: J2.S2, J3.S2
/S3: J2.S3, J3.S3
/S4: J2.S4, J3.S4
/S5: J2.S5, J3.S5
/S6: J2.S6, J3.S6
/S7: J2.S7, J3.S7
/SATA_PIN_11: J2.P11, Q1.2 (B), R1.2
/SENS_CADDY_CLOSED: J4.2, R4.1, U1.6
GND: J1.6, J2.P4, J2.P5, J2.P6, J2.P10, J2.P12, J2.SH (SHIELD), J3.P4, J3.P5, J3.P6, J3.P10, J3.P11, J3.P12, J3.SH (SHIELD), J4.5, R2.2, R3.2, U1.4 (V-)
unnamed: J2.P7, J3.P7
unnamed: J2.P8, J3.P8
unnamed: J2.P9, J3.P9
unnamed: J2.P13, J3.P13
unnamed: J2.P14, J3.P14
unnamed: J2.P15, J3.P15
unnamed: R3.1, R4.2, U1.2 (-)

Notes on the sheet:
red wire this way up

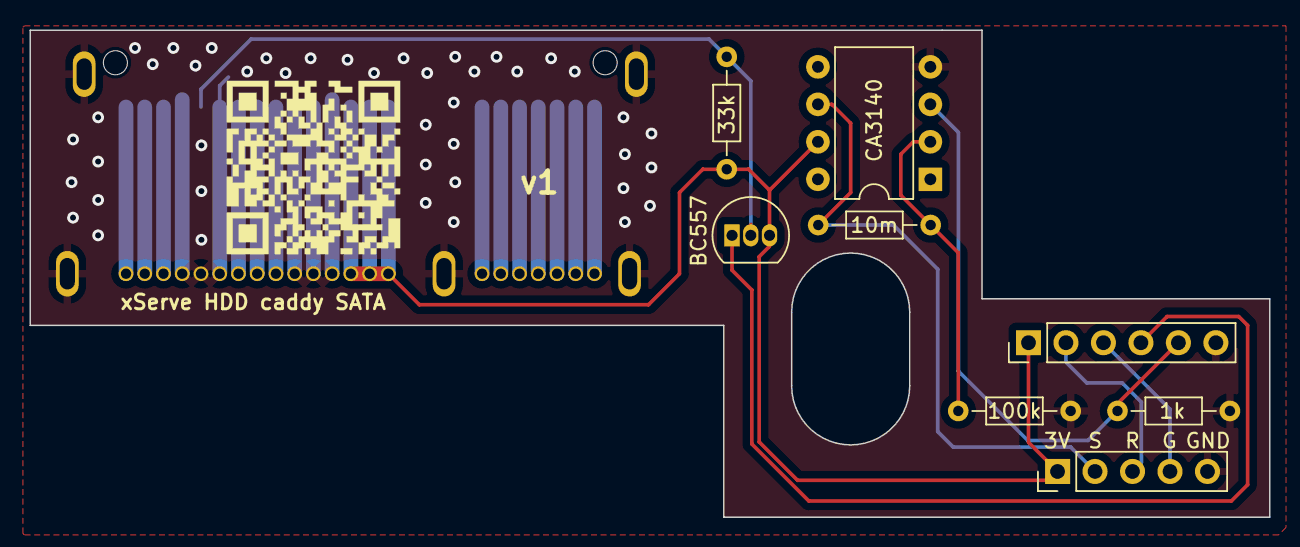
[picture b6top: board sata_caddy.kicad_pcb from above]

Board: 2 copper layers, 84.0 x 33.0 mm, 11 parts (1 on the bottom side), 22 nets.

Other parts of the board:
v1: LOGO; qr
